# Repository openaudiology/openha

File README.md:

# Project

This project provides the source files for a hearing aid device that can be used as a tool for embedded digital signal processing.
It is based on a Cortex M4 chip, with BLE and USB interfaces.

This project is supported by the non-profit organisation [Open Audiology](https://www.openaudiology.org) (French: Association loi 1901).

## Contents

The repository currently contains hardware and documentation files. The project is under active development with a targeted release in the Fall of 2018.

## Built With

* [Eagle CAD](https://www.autodesk.com/products/eagle/overview) - For electronic circuits and board routing.
* [Fusion 360](https://www.autodesk.com/products/fusion-360/overview) - 3D models

## Authors

* **Victor Benichoux** - *electronics* - Hearing researcher at [Institut Pasteur](https://research.pasteur.fr/en/member/victor-benichoux/). Contact me if you are interested in this project.
* **Grégory Gérenton** - *electronics* - Open Audiology.

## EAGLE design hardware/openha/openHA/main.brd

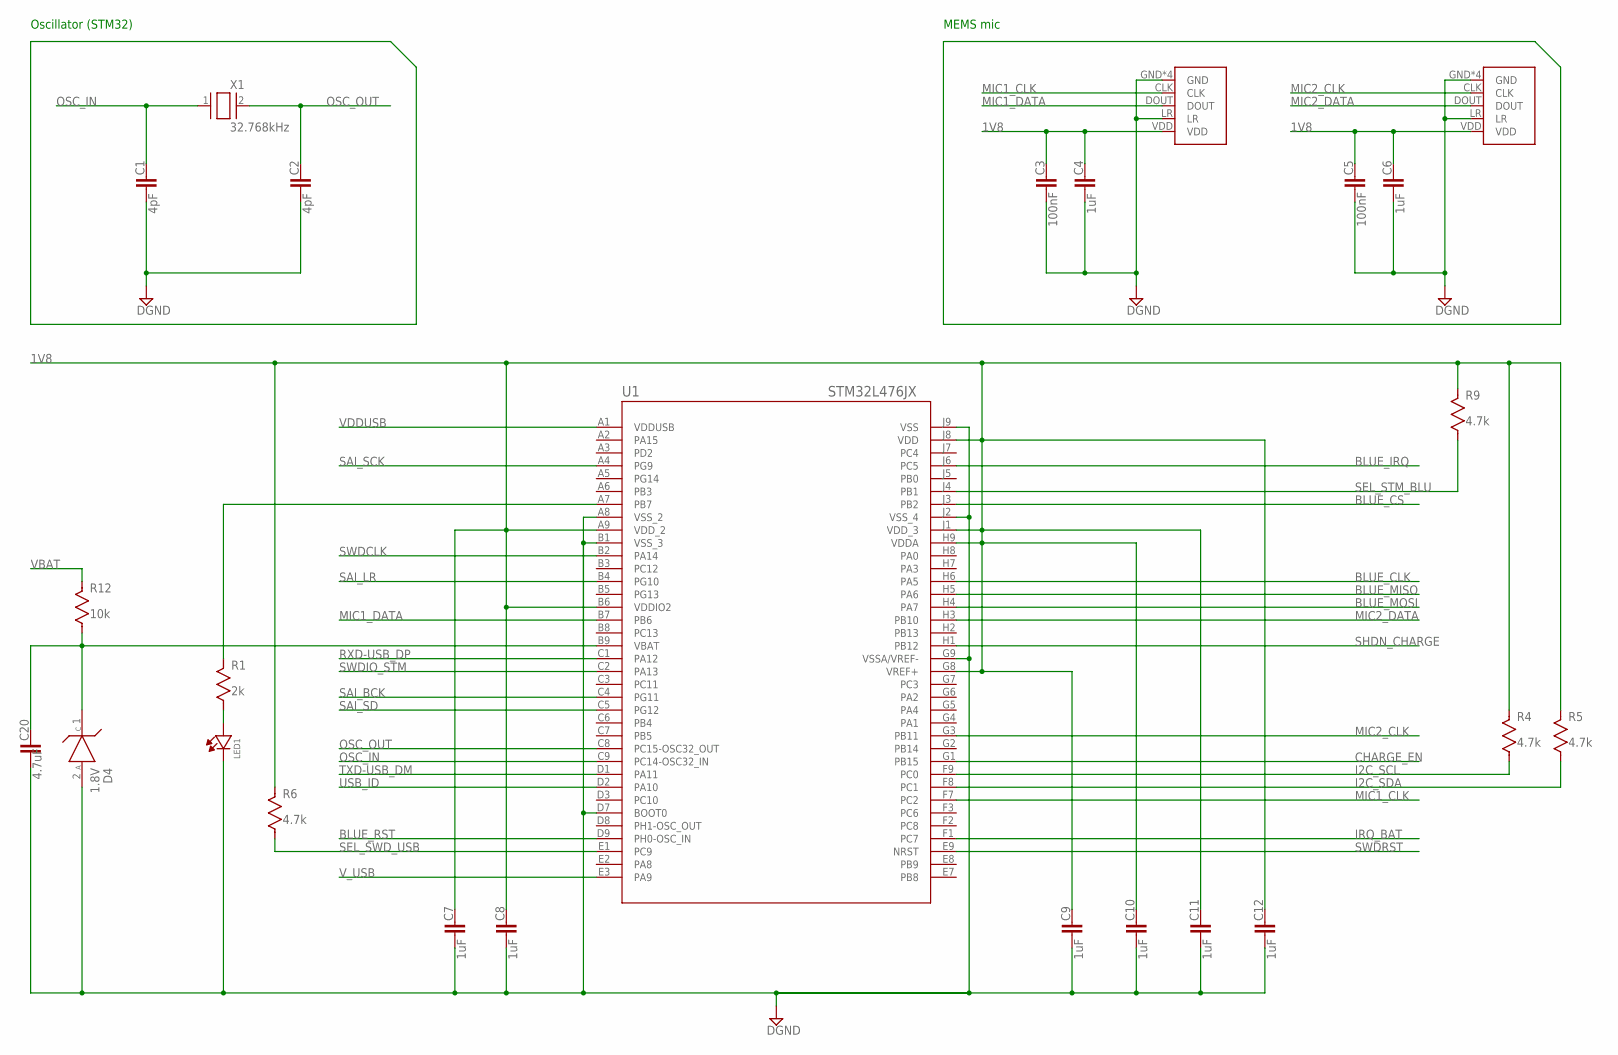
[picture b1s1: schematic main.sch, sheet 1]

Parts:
C1, C2: 4pF; 0201_X30
C3, C5: 100nF; 0201_X30
C4, C6, C7, C8, C9, C10, C11, C12: 1uF; 0201_X30
C20: 4.7uF; 0201_X30
D4: 1.8V; SOD-523
LED1: LED-KPG-0603; 0.65X0.35X0.2MM(0201)SMDCHIPLE
MIC1, MIC2: MP34DT05-A; MIC-PACK
R1: 2k; 0201_X30
R4, R5, R6, R9: 4.7k; 0201_X30
R12: 10k; 0201_X30
U1: STM32L476JX; WLCSP72
X1: 32.768kHz; ABS06-107

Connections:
1V8: C3.1, C4.1, C5.1, C6.1, C7.1, C8.1, C9.1, C10.1, C11.1, C12.1, MIC1.VDD, MIC2.VDD, R4.1, R5.1, R6.1, R9.1, U1.A9 (VDD_2), U1.B6 (VDDIO2), U1.G8 (VREF+), U1.H9 (VDDA), U1.J1 (VDD_3), U1.J8 (VDD); also elsewhere on the board
BLUE_CLK: U1.H6 (PA5); also elsewhere on the board
BLUE_CS: U1.J3 (PB2); also elsewhere on the board
BLUE_IRQ: U1.J6 (PC5); also elsewhere on the board
BLUE_MISO: U1.H5 (PA6); also elsewhere on the board
BLUE_MOSI: U1.H4 (PA7); also elsewhere on the board
BLUE_RST: U1.D9 (PH0-OSC_IN)
CHARGE_EN: U1.G1 (PB15); also elsewhere on the board
DGND: C1.2, C2.2, C3.2, C4.2, C5.2, C6.2, C7.2, C8.2, C9.2, C10.2, C11.2, C12.2, C20.2, D4.2 (ANODE), LED1.1 (K), MIC1.GND, MIC1.GND1 (GND), MIC1.GND2 (GND), MIC1.GND3 (GND), MIC1.LR, MIC2.GND, MIC2.GND1 (GND), MIC2.GND2 (GND), MIC2.GND3 (GND), MIC2.LR, U1.A8 (VSS_2), U1.B1 (VSS_3), U1.D7 (BOOT0), U1.G9 (VSSA/VREF-), U1.J2 (VSS_4), U1.J9 (VSS); also elsewhere on the board
I2C_SCL: R4.2, U1.F9 (PC0); also elsewhere on the board
I2C_SDA: R5.2, U1.F8 (PC1); also elsewhere on the board
IRQ_BAT: U1.F1 (PC7); also elsewhere on the board
MIC1_CLK: MIC1.CLK, U1.F7 (PC2)
MIC1_DATA: MIC1.DOUT, U1.B7 (PB6)
MIC2_CLK: MIC2.CLK, U1.G3 (PB11)
MIC2_DATA: MIC2.DOUT, U1.H3 (PB10)
unnamed: R1.1, U1.A7 (PB7)
unnamed: C20.1, D4.1 (CATHODE), R12.2, U1.B9 (VBAT)
unnamed: LED1.2 (A), R1.2
OSC_IN: C1.1, U1.C9 (PC14-OSC32_IN), X1.1
OSC_OUT: C2.1, U1.C8 (PC15-OSC32_OUT), X1.2
RXD-USB_DP: U1.C1 (PA12); also elsewhere on the board
SAI_BCK: U1.C4 (PG11); also elsewhere on the board
SAI_LR: U1.B4 (PG10); also elsewhere on the board
SAI_SCK: U1.A4 (PG9); also elsewhere on the board
SAI_SD: U1.C5 (PG12); also elsewhere on the board
SEL_STM_BLU: R9.2, U1.J4 (PB1); also elsewhere on the board
SEL_SWD_USB: R6.2, U1.E1 (PC9); also elsewhere on the board
SHDN_CHARGE: U1.H1 (PB12); also elsewhere on the board
SWDCLK: U1.B2 (PA14); also elsewhere on the board
SWDIO_STM: U1.C2 (PA13); also elsewhere on the board
SWDRST: U1.E9 (NRST); also elsewhere on the board
TXD-USB_DM: U1.D1 (PA11); also elsewhere on the board
USB_ID: U1.D2 (PA10); also elsewhere on the board
VBAT: R12.1; also elsewhere on the board
VDDUSB: U1.A1 (VDDUSB); also elsewhere on the board
V_USB: U1.E3 (PA9); also elsewhere on the board

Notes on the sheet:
Oscillator (STM32)
MEMS mic

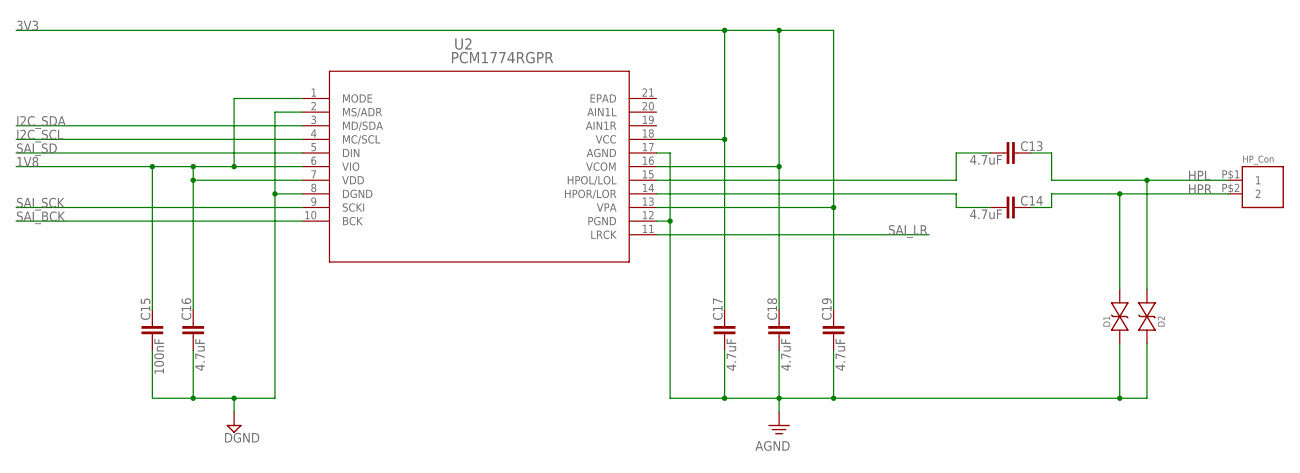
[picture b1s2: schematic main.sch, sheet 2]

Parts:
C13, C14, C16, C17, C18, C19: 4.7uF; 0201_X30
C15: 100nF; 0201_X30
D1, D2: TVS_DIODE_B; 0201_X30
J1: HP_Con; 2PINCON
U2: PCM1774RGPR; RGP20_2P7X2P7

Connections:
1V8: C15.2, C16.2, U2.1 (MODE), U2.6 (VIO), U2.7 (VDD); also elsewhere on the board
3V3: C17.2, C18.2, C19.2, U2.13 (VPA), U2.16 (VCOM), U2.18 (VCC); also elsewhere on the board
AGND: C17.1, C18.1, C19.1, D1.2 (K), D2.2 (K), U2.12 (PGND), U2.17 (AGND); also elsewhere on the board
DGND: C15.1, C16.1, U2.2 (MS/ADR), U2.8 (DGND); also elsewhere on the board
HPL: C13.2, D2.1 (A), J1.P$1 (1)
HPR: C14.2, D1.1 (A), J1.P$2 (2)
I2C_SCL: U2.4 (MC/SCL); also elsewhere on the board
I2C_SDA: U2.3 (MD/SDA); also elsewhere on the board
unnamed: C13.1, U2.15 (HPOL/LOL)
unnamed: C14.1, U2.14 (HPOR/LOR)
SAI_BCK: U2.10 (BCK); also elsewhere on the board
SAI_LR: U2.11 (LRCK); also elsewhere on the board
SAI_SCK: U2.9 (SCKI); also elsewhere on the board
SAI_SD: U2.5 (DIN); also elsewhere on the board

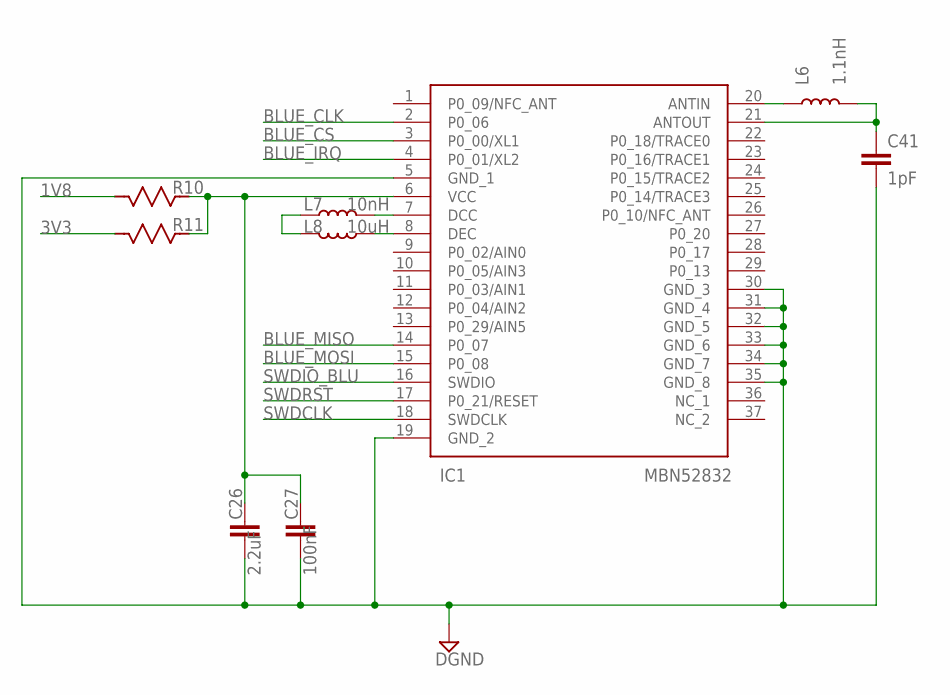
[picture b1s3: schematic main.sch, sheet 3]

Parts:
C26: 2.2uF; 0201_X30
C27: 100nF; 0201_X30
C41: 1pF; 0201_X30
IC1: MBN52832
L6: 1.1nH; 0201_X30
L7: 10nH; C0402K
L8: 10uH; C0603K
R10, R11: R; 0201_X30

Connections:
1V8: R10.1; also elsewhere on the board
3V3: R11.1; also elsewhere on the board
BLUE_CLK: IC1.2 (P0_06); also elsewhere on the board
BLUE_CS: IC1.3 (P0_00/XL1); also elsewhere on the board
BLUE_IRQ: IC1.4 (P0_01/XL2); also elsewhere on the board
BLUE_MISO: IC1.14 (P0_07); also elsewhere on the board
BLUE_MOSI: IC1.15 (P0_08); also elsewhere on the board
DGND: C26.2, C27.2, C41.2, IC1.5 (GND_1), IC1.19 (GND_2), IC1.30 (GND_3), IC1.31 (GND_4), IC1.32 (GND_5), IC1.33 (GND_6), IC1.34 (GND_7), IC1.35 (GND_8); also elsewhere on the board
unnamed: C41.1, IC1.21 (ANTOUT), L6.2
unnamed: C26.1, C27.1, IC1.6 (VCC), R10.2, R11.2
unnamed: IC1.20 (ANTIN), L6.1
unnamed: IC1.7 (DCC), L7.2
unnamed: IC1.8 (DEC), L8.1
unnamed: L7.1, L8.2
SWDCLK: IC1.18 (SWDCLK); also elsewhere on the board
SWDIO_BLU: IC1.16 (SWDIO); also elsewhere on the board
SWDRST: IC1.17 (P0_21/RESET); also elsewhere on the board

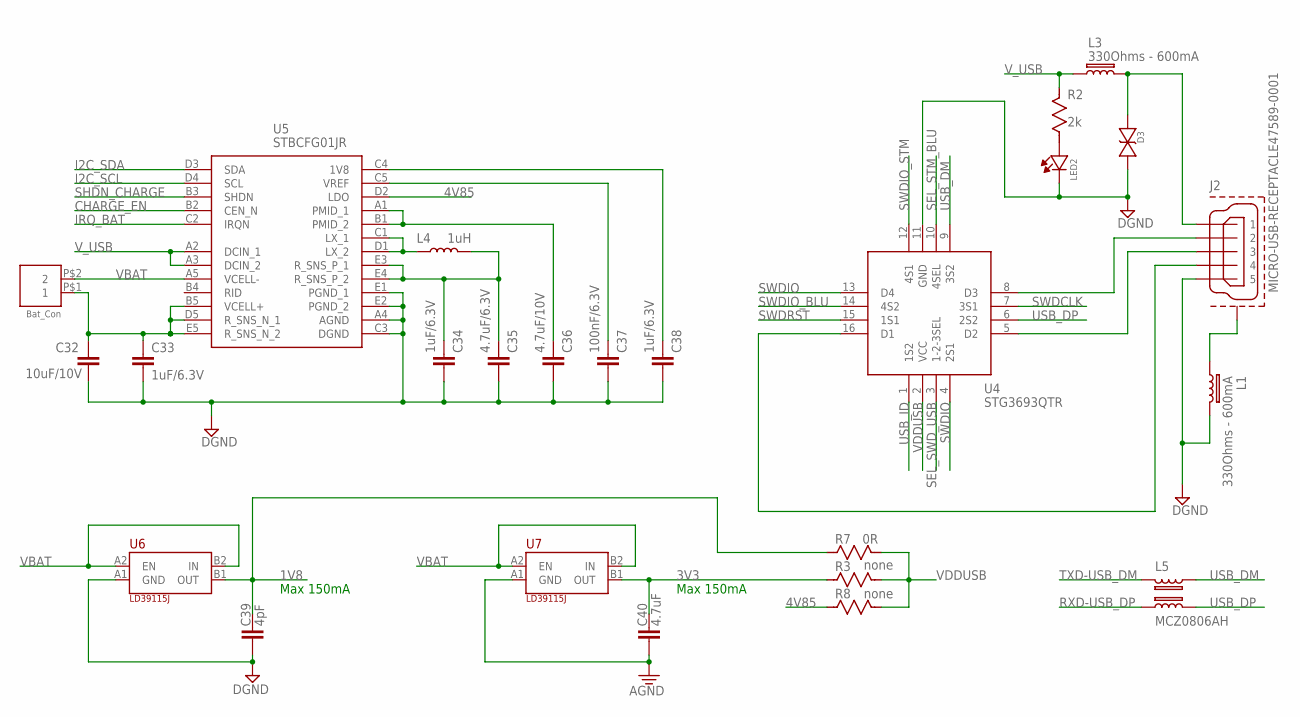
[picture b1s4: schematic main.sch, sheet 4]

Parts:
C32: 10uF/10V; 0201_X30
C33, C34, C38: 1uF/6.3V; 0201_X30
C35: 4.7uF/6.3V; 0201_X30
C36: 4.7uF/10V; 0201_X30
C37: 100nF/6.3V; 0201_X30
C39: 4pF; 0201_X30
C40: 4.7uF; 0201_X30
D3: TVS_DIODE_B; 0201_X30
J2: MICRO-USB-RECEPTACLE47589-0001; 47589-0001
J3: Bat_Con; 2PINCON
L1, L3: 330Ohms - 600mA; C0402
L4: 1uH; 0201_X30
L5: MCZ0806AH; 0302
LED2: LED-KPG-0603; 0.65X0.35X0.2MM(0201)SMDCHIPLE
R2: 2k; 0201_X30
R3, R8: none; 0201_X30
R7: 0R; 0201_X30
U4: STG3693QTR; QFN40P180X260X55-17N
U5: STBCFG01JR; BGA25C40P5X5_219X228X60
U6, U7: LD39115J; FLIPCHIP-2

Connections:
1V8: C39.1, R7.2, U6.B1 (OUT); also elsewhere on the board
3V3: C40.1, R3.2, U7.B1 (OUT); also elsewhere on the board
4V85: R8.2, U5.D2 (LDO)
AGND: C40.2, U7.A1 (GND); also elsewhere on the board
CHARGE_EN: U5.B2 (CEN_N); also elsewhere on the board
DGND: C32.2, C33.2, C34.2, C35.2, C36.2, C37.2, C38.2, C39.2, D3.2 (K), J2.5, L1.2, LED2.1 (K), U4.11 (GND), U5.A4 (AGND), U5.C3 (DGND), U5.E1 (PGND_1), U5.E2 (PGND_2), U6.A1 (GND); also elsewhere on the board
I2C_SCL: U5.D4 (SCL); also elsewhere on the board
I2C_SDA: U5.D3 (SDA); also elsewhere on the board
IRQ_BAT: U5.C2 (IRQN); also elsewhere on the board
unnamed: LED2.2 (A), R2.2
unnamed: C37.1, U5.C5 (VREF)
unnamed: J2.CASING1 (CASE), J2.CASING2 (CASE), J2.CASING3 (CASE), J2.CASING4 (CASE), J2.CASING5 (CASE), J2.CASING6 (CASE), J2.CASING7 (CASE), J2.CASING8 (CASE), L1.1
unnamed: J2.2, U4.8 (D3)
unnamed: J2.3, U4.5 (D2)
unnamed: D3.1 (A), J2.1, L3.2
unnamed: J2.4, U4.16 (D1)
unnamed: C38.1, U5.C4 (1V8)
unnamed: C36.1, U5.A1 (PMID_1), U5.B1 (PMID_2)
unnamed: C34.1, C35.1, L4.2, U5.E3 (R_SNS_P_1), U5.E4 (R_SNS_P_2)
unnamed: L4.1, U5.C1 (LX_1), U5.D1 (LX_2)
unnamed: C32.1, C33.1, J3.P$1 (1), U5.B5 (VCELL+), U5.D5 (R_SNS_N_1), U5.E5 (R_SNS_N_2)
RXD-USB_DP: L5.2; also elsewhere on the board
SEL_STM_BLU: U4.10 (4SEL); also elsewhere on the board
SEL_SWD_USB: U4.3 (1-2-3SEL); also elsewhere on the board
SHDN_CHARGE: U5.B3 (SHDN); also elsewhere on the board
SWDCLK: U4.7 (3S1); also elsewhere on the board
SWDIO: U4.4 (2S1), U4.13 (D4)
SWDIO_BLU: U4.14 (4S2); also elsewhere on the board
SWDIO_STM: U4.12 (4S1); also elsewhere on the board
SWDRST: U4.15 (1S1); also elsewhere on the board
TXD-USB_DM: L5.1; also elsewhere on the board
USB_DM: L5.4, U4.9 (3S2)
USB_DP: L5.3, U4.6 (2S2)
USB_ID: U4.1 (1S2); also elsewhere on the board
VBAT: J3.P$2 (2), U5.A5 (VCELL-), U6.A2 (EN), U6.B2 (IN), U7.A2 (EN), U7.B2 (IN); also elsewhere on the board
VDDUSB: R3.1, R7.1, R8.1, U4.2 (VCC); also elsewhere on the board
V_USB: L3.1, R2.1, U5.A2 (DCIN_1), U5.A3 (DCIN_2); also elsewhere on the board

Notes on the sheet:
Max 150mA

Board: 4 copper layers, 70 parts (4 on the bottom side), 65 nets, no tracks yet.

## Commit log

2018-08-02 fixed readme
2018-08-16 Initial corrections
    Miscellaneous corrections of the initial commit
2018-08-17 Add some datasheet
2018-10-11 Various BOM update
    Replace 4pin micro connector by USB (used for USB and SWD)
    Update BOM for LED, Crystal, Self and 3V3 LDO
2018-10-15 WIP-BOM Update
    Update BOM for battery charger and gauge
2018-10-17 WIP-BOM Update
    Replace Bluetooth chips by a fully integrated module
2018-10-17 Define design rules
    Setup Eurocircuit standard 4 layer design rules
2018-10-19 WIP-BOM Update
    Update USB case
2018-10-24 Footprint update
    Update some footprint

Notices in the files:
parts and their libraries:
OAlib: (C) 2014 Tomasz Boleslaw CEDRO, cederom@tlen.pl, http://www.tomek.cedro.info.
